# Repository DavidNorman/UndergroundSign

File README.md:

# UndergroundSign
An ESP32S2 / HUB75 project to display London Underground arrival estimates on an LED matrix display

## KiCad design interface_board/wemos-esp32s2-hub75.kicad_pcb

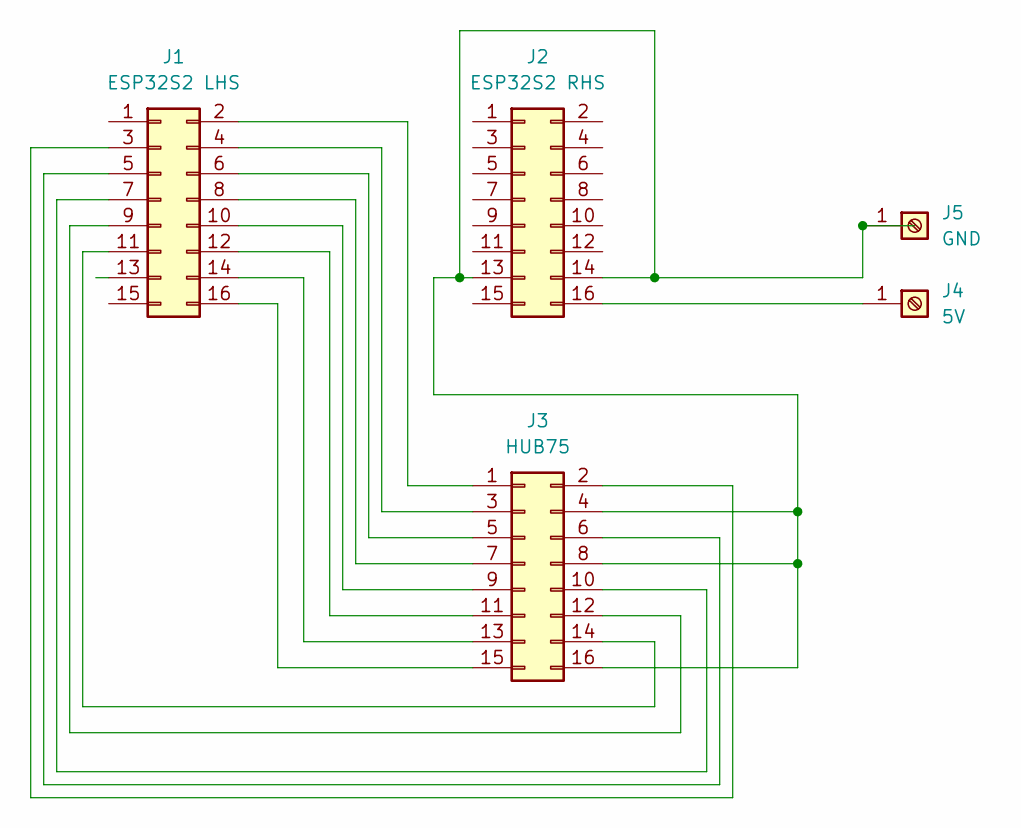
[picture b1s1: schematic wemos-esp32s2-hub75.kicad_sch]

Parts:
J1: ESP32S2 LHS; PinHeader_2x08_P2.54mm_Vertical
J2: ESP32S2 RHS; PinHeader_2x08_P2.54mm_Vertical
J3: HUB75; PinHeader_2x08_P2.54mm_Vertical
J4: 5V; MountingHole_3.2mm_M3_Pad_TopBottom
J5: GND; MountingHole_3.2mm_M3_Pad_TopBottom

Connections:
unnamed: J1.2, J3.1
unnamed: J1.3, J3.2
unnamed: J1.4, J3.3
unnamed: J1.5, J3.6
unnamed: J1.6, J3.5
unnamed: J1.7, J3.10
unnamed: J1.8, J3.7
unnamed: J1.9, J3.12
unnamed: J1.10, J3.9
unnamed: J1.11, J3.14
unnamed: J1.12, J3.11
unnamed: J1.14, J3.13
unnamed: J1.16, J3.15
unnamed: J2.13, J2.14, J3.4, J3.8, J3.16, J5.1 (Pin_1_1)
unnamed: J2.16, J4.1 (Pin_1_1)

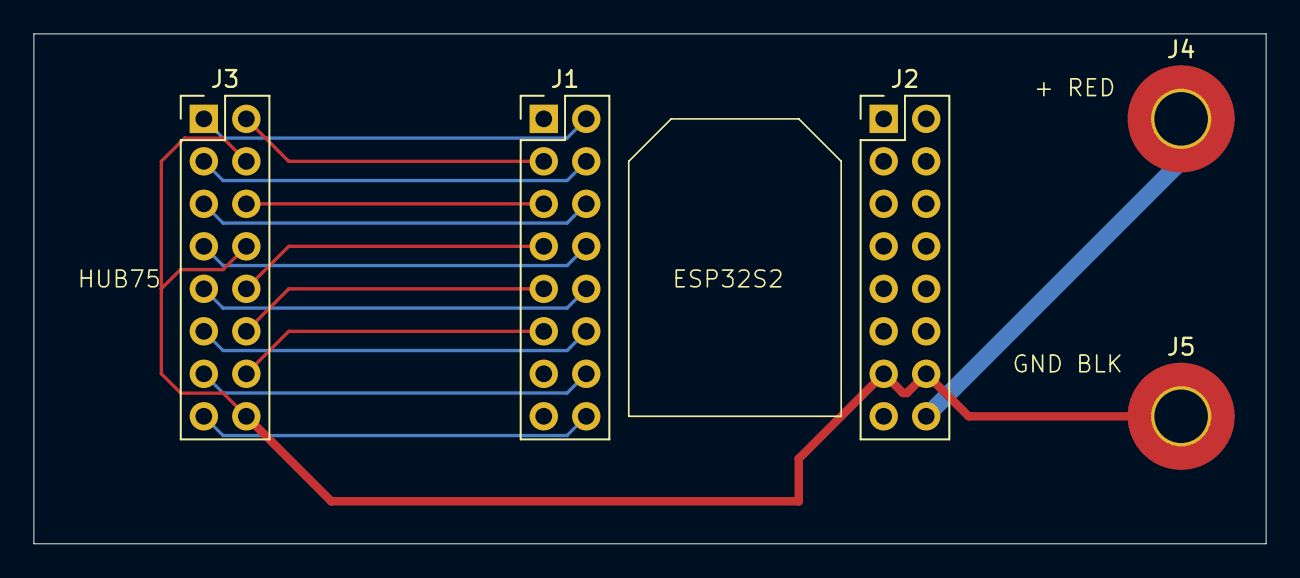
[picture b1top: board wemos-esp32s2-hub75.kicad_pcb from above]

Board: 2 copper layers, 73.7 x 30.5 mm, 5 parts (0 on the bottom side), 15 nets.

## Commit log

2026-03-27 Adding sketch and moving font to a subdir
2026-03-27 Create Font_Licence
    Adding the licence info for the Font repo
2026-03-29 Adding a fetch of the time, and printing of it on line 4 Now 3 pages of trains Don't abort when a record doesn't contain all fields - sometimes random spurious entries exist Use a different JSON libr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
2026-04-18 Use timer task for update
2026-04-18 Use a timer to refresh the clock too
2026-05-01 More robust response to errors
2026-06-08 Update to include a web interface for configuration.
2026-06-08 Add a test program to drive the test board
2026-06-16 Adding interface board CAD files
2026-06-16 Move file
2026-06-16 move files into arduino compatible subdirs
